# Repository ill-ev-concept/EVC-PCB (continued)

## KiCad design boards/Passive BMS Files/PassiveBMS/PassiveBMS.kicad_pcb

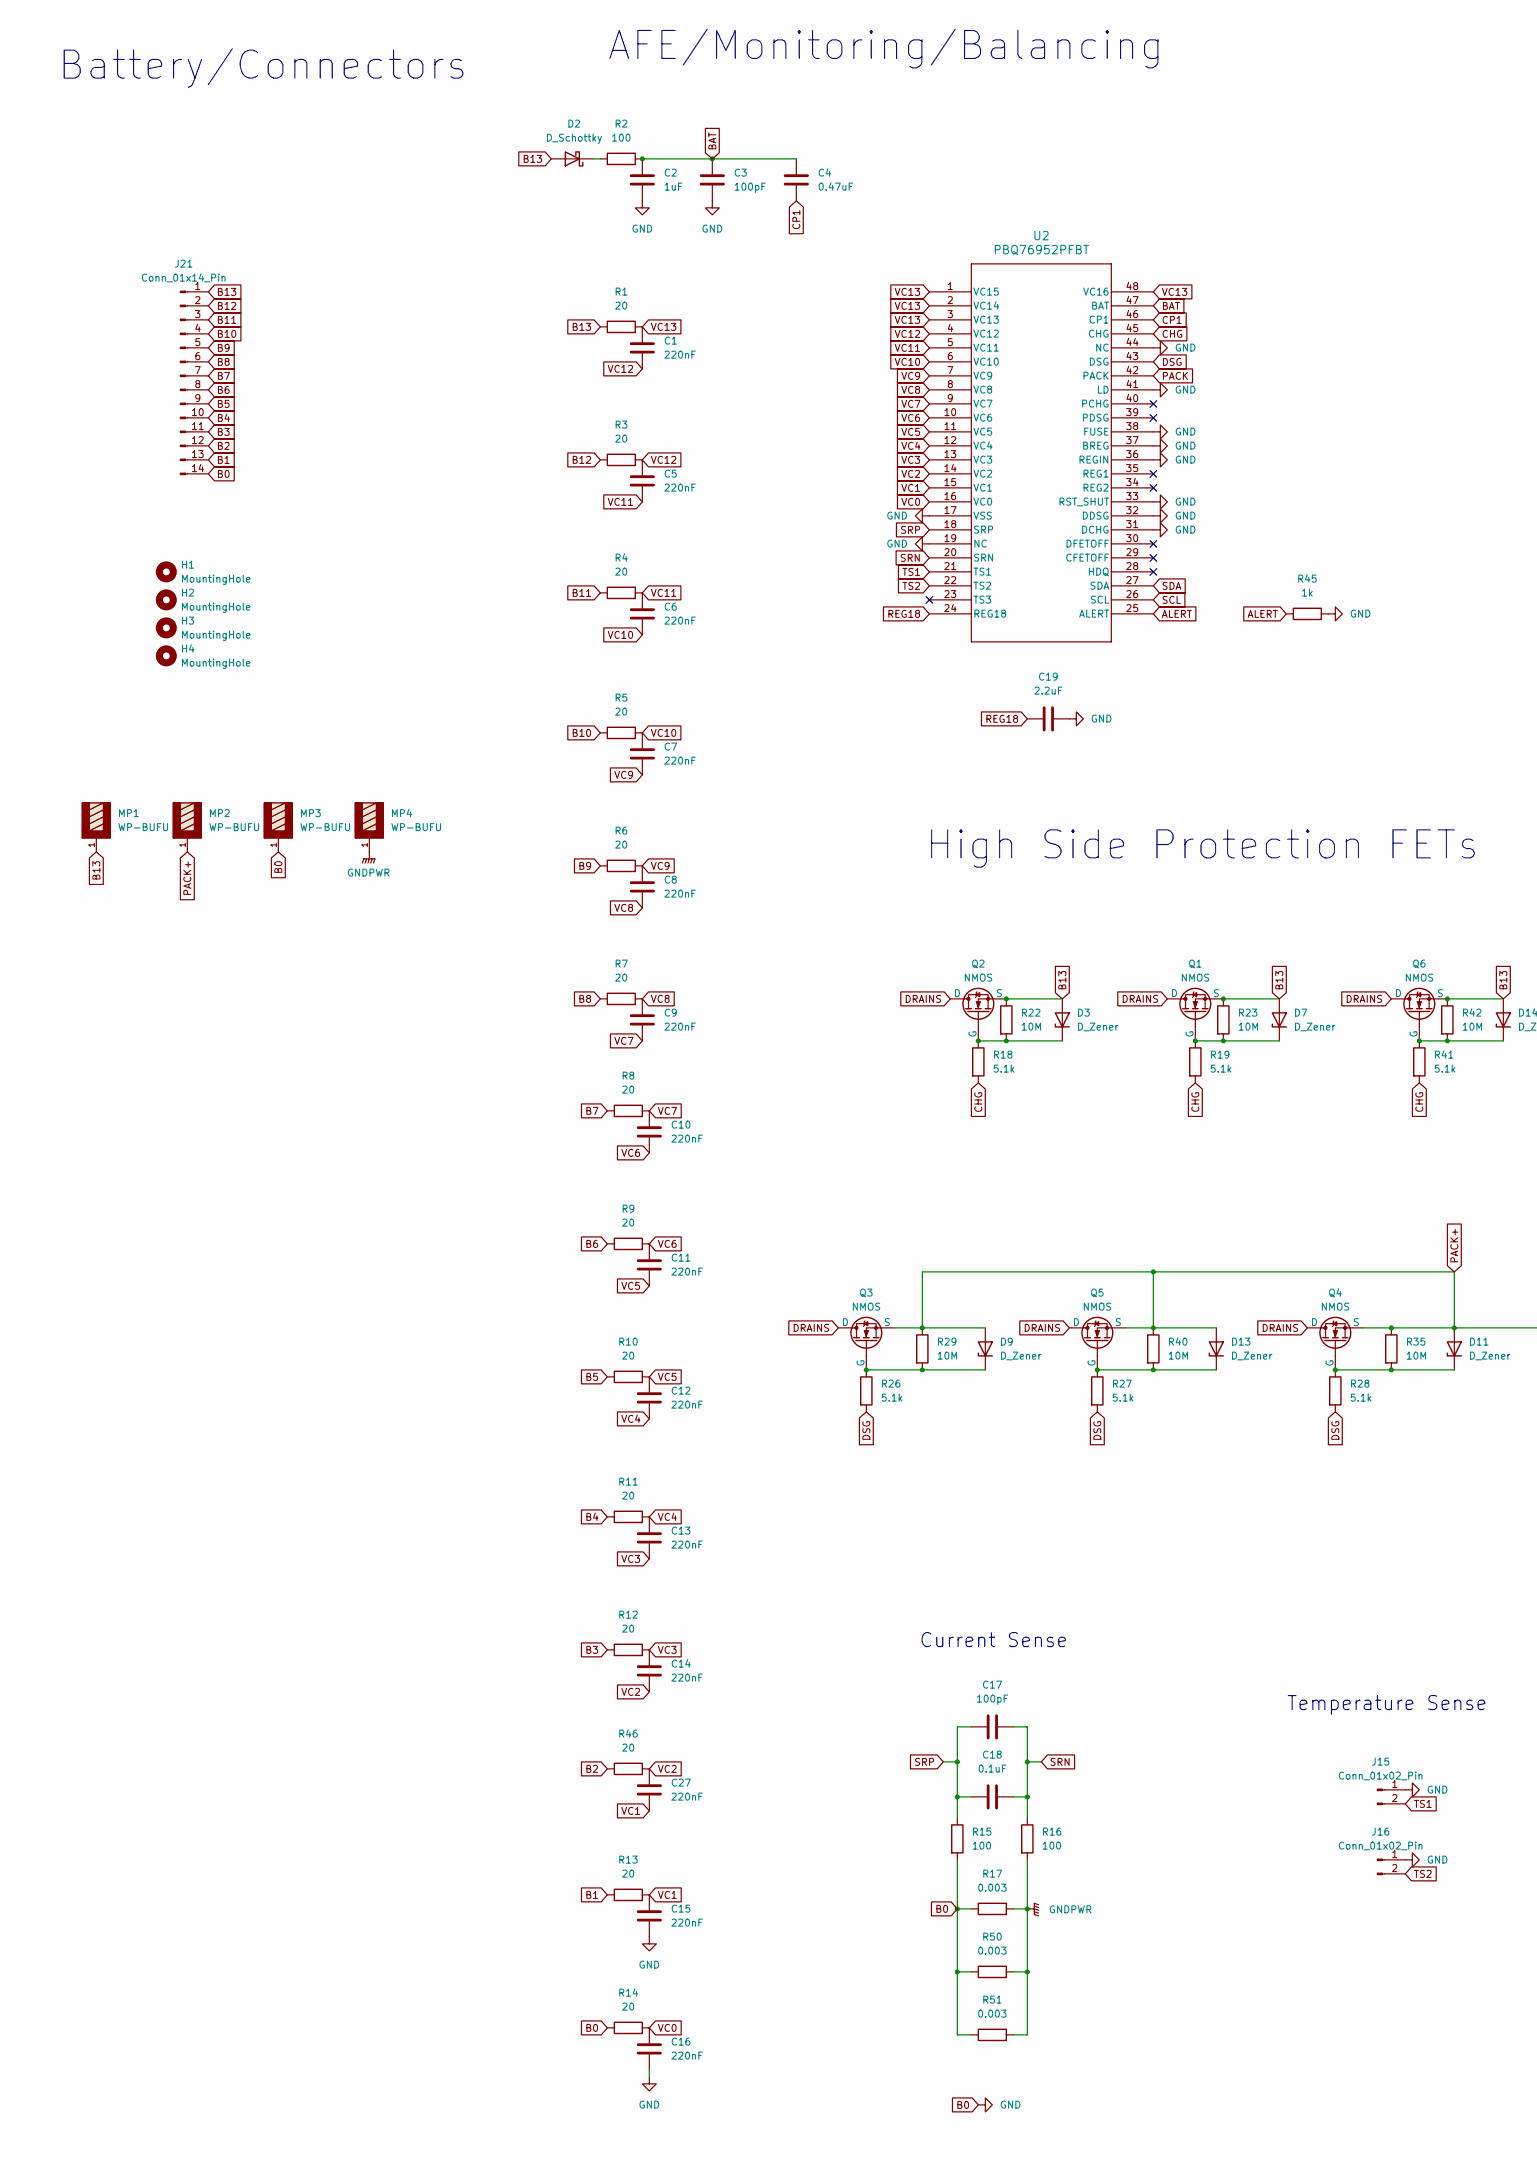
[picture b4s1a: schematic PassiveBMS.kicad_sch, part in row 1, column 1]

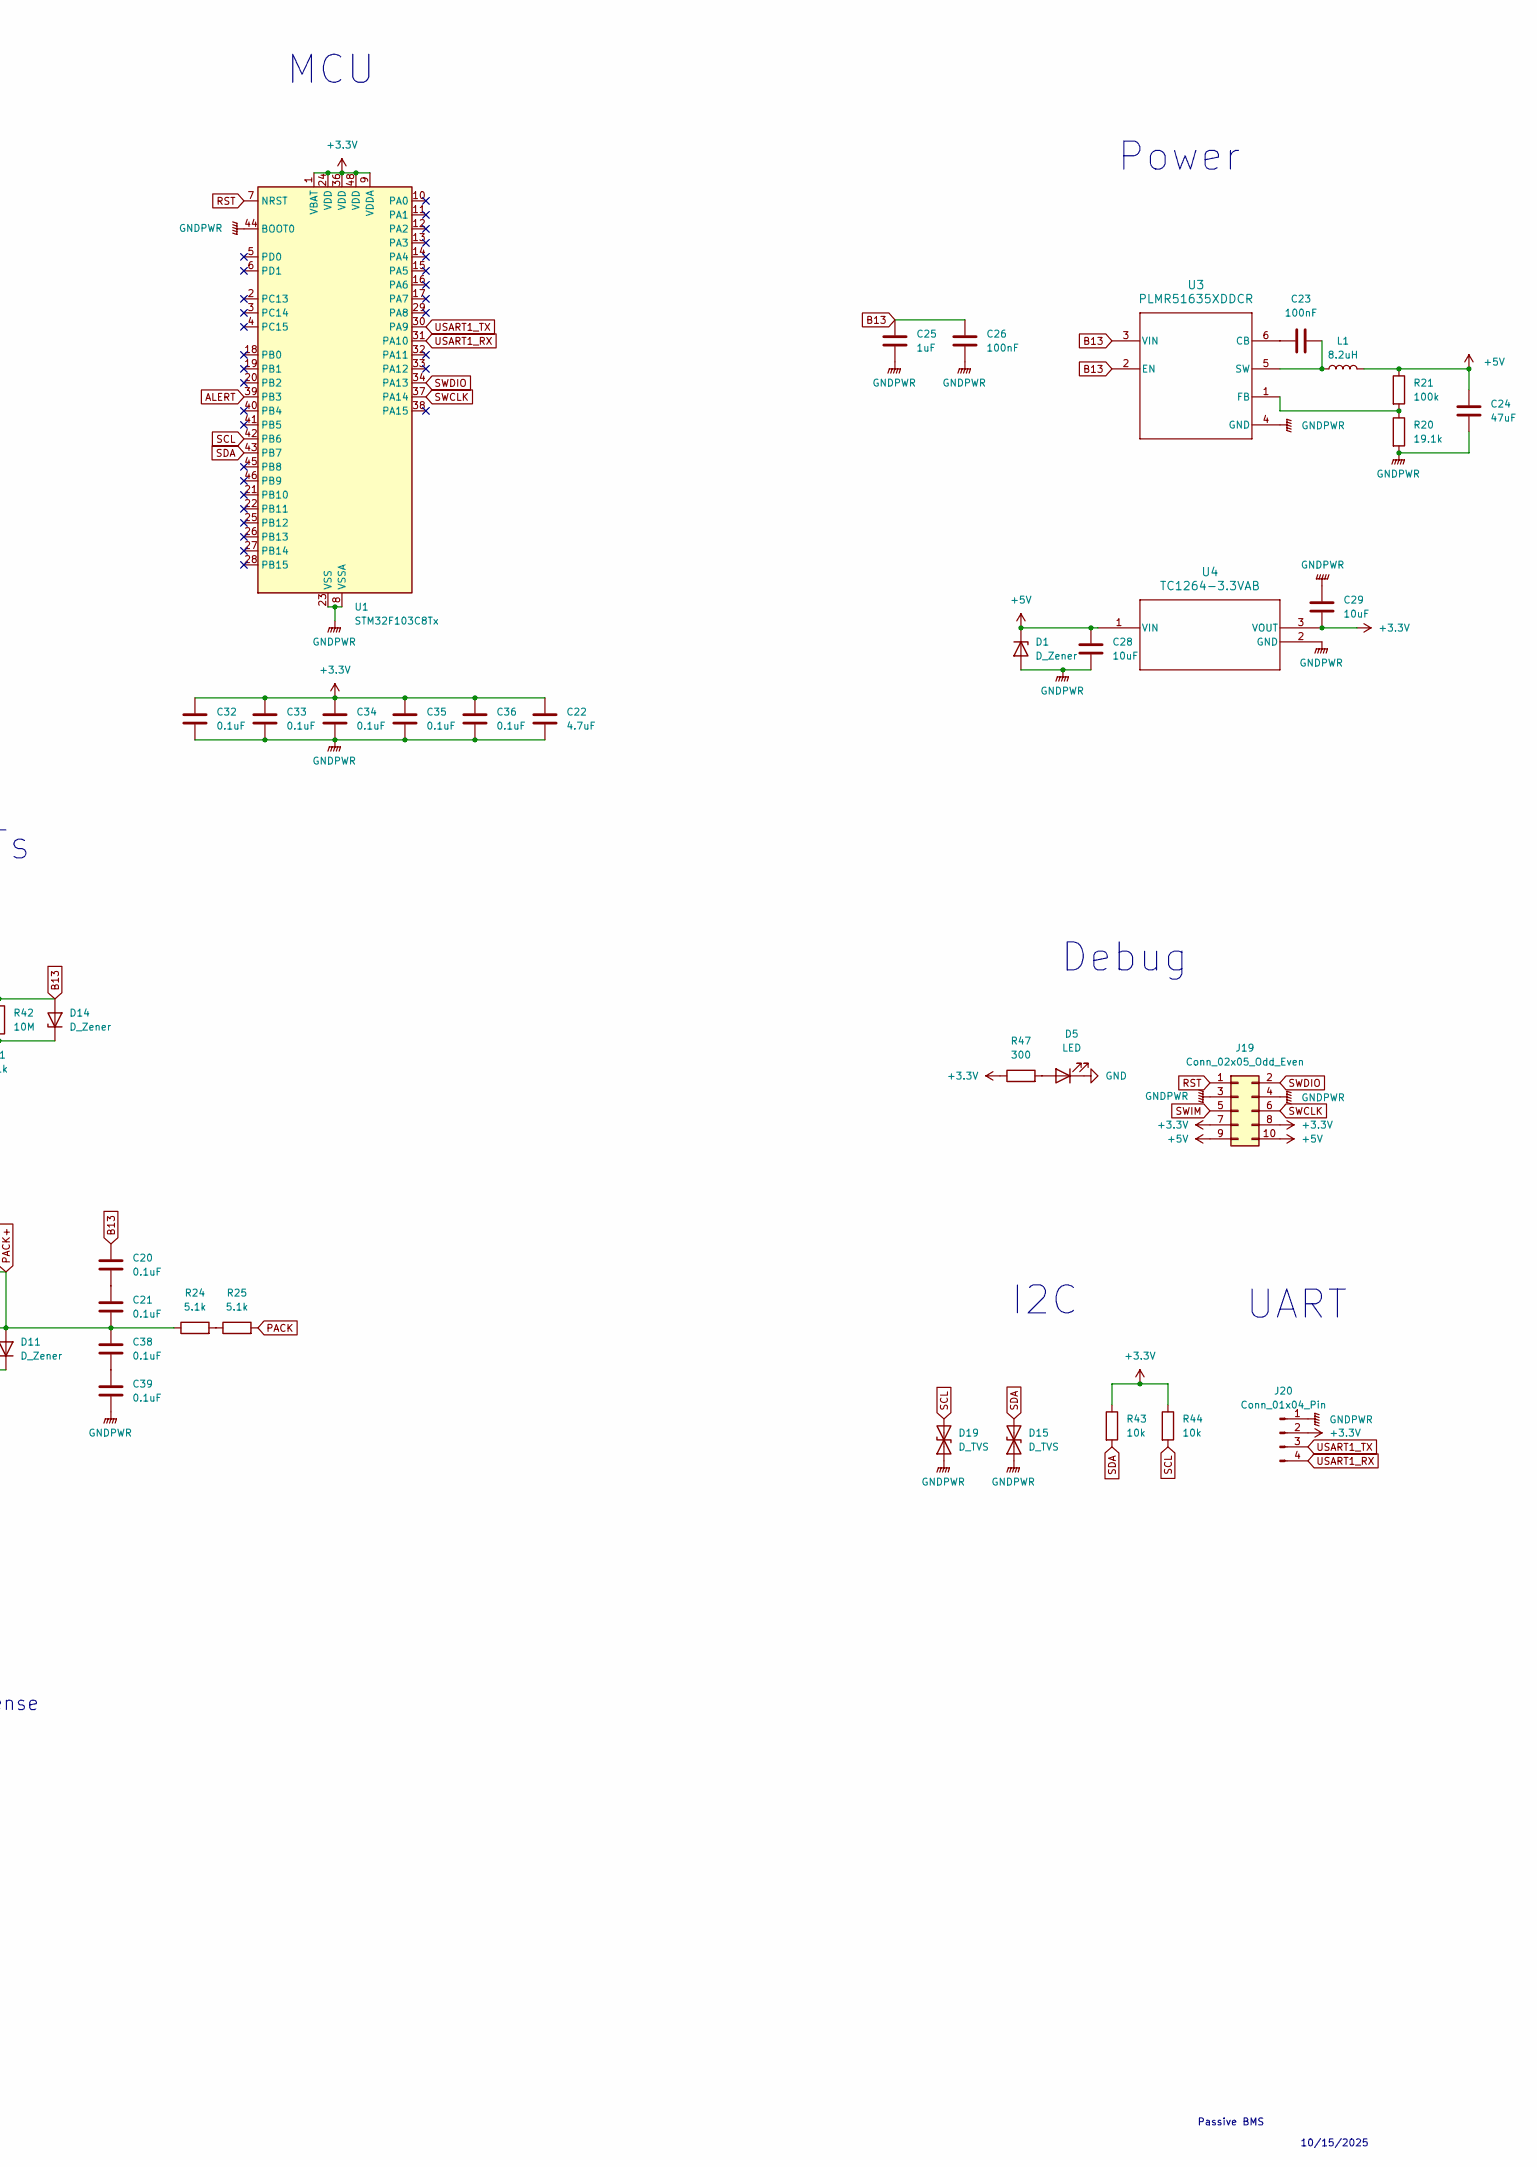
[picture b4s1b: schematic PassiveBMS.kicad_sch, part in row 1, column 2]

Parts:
C1, C5, C6, C7, C8, C9, C10, C11, C12, C13, C14, C15, C16, C27: 220nF; C_0402_1005Metric
C2, C25: 1uF; C_1206_3216Metric
C3: 100pF; C_1206_3216Metric
C4: 0.47uF; C_1206_3216Metric
C17: 100pF; C_0603_1608Metric
C18, C20, C21, C32, C33, C34, C35, C36: 0.1uF; C_0603_1608Metric
C19: 2.2uF; C_0603_1608Metric
C22: 4.7uF; C_0603_1608Metric
C23, C26: 100nF; C_1206_3216Metric
C24: 47uF; C_0402_1005Metric
C28, C29: 10uF; C_0603_1608Metric
C38, C39: 0.1uF; R_1206_3216Metric
D1: D_Zener; R_0805_2012Metric
D2: D_Schottky; D_SOD-123F
D3, D7, D9, D11, D13, D14: D_Zener; D_SOD-123
D5: LED; LED_0603_1608Metric
D15, D19: D_TVS; D_SOD-323
H1, H2, H3, H4: MountingHole; MountingHole_2.5mm
J15, J16: Conn_01x02_Pin; PinHeader_1x02_P2.54mm_Vertical
J19: Conn_02x05_Odd_Even; PinHeader_2x05_P2.54mm_Vertical
J20: Conn_01x04_Pin; PinHeader_1x04_P2.54mm_Vertical
J21: Conn_01x14_Pin; PinHeader_1x14_P2.54mm_Vertical
L1: 8.2uH; L_Bourns_SRR1260
MP1, MP2, MP3, MP4: WP-BUFU; screw connector
Q1, Q2, Q3, Q4, Q5, Q6: NMOS; fets
R1, R3, R4, R5, R6, R7, R8, R9, R10, R11, R12, R13, R14, R46: 20; R_0402_1005Metric
R2, R15, R16: 100; R_0603_1608Metric
R17, R50, R51: 0.003; R_Shunt_Vishay_WSR2_WSR3_KelvinConnection
R18, R19, R24, R25, R26, R27, R28, R41: 5.1k; R_0603_1608Metric
R20: 19.1k; R_0603_1608Metric
R21: 100k; R_0603_1608Metric
R22, R23, R29, R35, R40, R42: 10M; R_0603_1608Metric
R43, R44: 10k; R_0603_1608Metric
R45: 1k; R_0603_1608Metric
R47: 300; R_0603_1608Metric
U1: STM32F103C8Tx; LQFP-48_7x7mm_P0.5mm
U2: PBQ76952PFBT; TQFP-48_7x7mm_P0.5mm
U3: PLMR51635XDDCR; DDC0006A-MFG
U4: TC1264-3.3VAB; SOT-223-3_TabPin2

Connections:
+3.3V: C22.1, C29.2, C32.1, C33.1, C34.1, C35.1, C36.1, J19.7, J19.8, J20.2, R43.1, R44.1, R47.1, U1.1 (VBAT), U1.9 (VDDA), U1.24 (VDD), U1.36 (VDD), U1.48 (VDD), U4.3 (VOUT)
+5V: C24.2, C28.1, D1.1 (K), J19.9, J19.10, L1.2, R21.1, U4.1 (VIN)
ALERT: R45.1, U1.39 (PB3), U2.25 (ALERT)
B0: C2.2, C3.2, C15.2, C16.2, C19.2, D5.1 (K), J15.1, J16.1, J21.14, MP3.1, MP3.2, MP3.3, MP3.4, MP3.5, MP3.6, MP3.7, MP3.8, MP3.9, MP3.10, MP3.11, MP3.12, MP3.13, MP3.14, MP3.15, MP3.16, R14.1, R15.2, R17.1, R45.2, R50.1, R51.1, U2.17 (VSS), U2.19 (NC), U2.31 (DCHG), U2.32 (DDSG), U2.33 (RST_SHUT), U2.36 (REGIN), U2.37 (BREG), U2.38 (FUSE), U2.41 (LD), U2.44 (NC)
B1: J21.13, R13.1
B2: J21.12, R46.1
B3: J21.11, R12.1
B4: J21.10, R11.1
B5: J21.9, R10.1
B6: J21.8, R9.1
B7: J21.7, R8.1
B8: J21.6, R7.1
B9: J21.5, R6.1
B10: J21.4, R5.1
B11: J21.3, R4.1
B12: J21.2, R3.1
B13: C20.1, C25.1, C26.1, D2.2 (A), D3.2 (A), D7.2 (A), D14.2 (A), J21.1, MP1.1, MP1.2, MP1.3, MP1.4, MP1.5, MP1.6, MP1.7, MP1.8, MP1.9, MP1.10, MP1.11, MP1.12, MP1.13, MP1.14, MP1.15, MP1.16, Q1.3 (S), Q2.3 (S), Q6.3 (S), R1.1, R22.1, R23.1, R42.1, U3.2 (EN), U3.3 (VIN)
BAT: C2.1, C3.1, C4.1, R2.2, U2.47 (BAT)
CHG: R18.2, R19.2, R41.2, U2.45 (CHG)
CP1: C4.2, U2.46 (CP1)
DRAINS: Q1.1 (D), Q2.1 (D), Q3.1 (D), Q4.1 (D), Q5.1 (D), Q6.1 (D)
DSG: R26.2, R27.2, R28.2, U2.43 (DSG)
GNDPWR: C22.2, C24.1, C25.2, C26.2, C28.2, C29.1, C32.2, C33.2, C34.2, C35.2, C36.2, C39.2, D1.2 (A), D15.1 (A1), D19.1 (A1), J19.3, J19.4, J20.1, MP4.1, MP4.2, MP4.3, MP4.4, MP4.5, MP4.6, MP4.7, MP4.8, MP4.9, MP4.10, MP4.11, MP4.12, MP4.13, MP4.14, MP4.15, MP4.16, R16.2, R17.2, R20.2, R50.2, R51.2, U1.8 (VSSA), U1.23 (VSS), U1.35 (VSS), U1.44 (BOOT0), U1.47 (VSS), U3.4 (GND), U4.2 (GND)
unnamed: C20.2, C21.1
unnamed: C38.2, C39.1
unnamed: D2.1 (K), R2.1
unnamed: D3.1 (K), Q2.2 (G), R18.1, R22.2
unnamed: D5.2 (A), R47.2
unnamed: D7.1 (K), Q1.2 (G), R19.1, R23.2
unnamed: D9.1 (K), Q3.2 (G), R26.1, R29.2
unnamed: D11.1 (K), Q4.2 (G), R28.1, R35.2
unnamed: D13.1 (K), Q5.2 (G), R27.1, R40.2
unnamed: D14.1 (K), Q6.2 (G), R41.1, R42.2
unnamed: R24.2, R25.1
unnamed: C23.1, U3.6 (CB)
unnamed: R20.1, R21.2, U3.1 (FB)
unnamed: C23.2, L1.1, U3.5 (SW)
PACK: R25.2, U2.42 (PACK)
PACK+: C21.2, C38.1, D9.2 (A), D11.2 (A), D13.2 (A), MP2.1, MP2.2, MP2.3, MP2.4, MP2.5, MP2.6, MP2.7, MP2.8, MP2.9, MP2.10, MP2.11, MP2.12, MP2.13, MP2.14, MP2.15, MP2.16, Q3.3 (S), Q4.3 (S), Q5.3 (S), R24.1, R29.1, R35.1, R40.1
REG18: C19.1, U2.24 (REG18)
RST: J19.1, U1.7 (NRST)
SCL: D19.2 (A2), R44.2, U1.42 (PB6), U2.26 (SCL)
SDA: D15.2 (A2), R43.2, U1.43 (PB7), U2.27 (SDA)
SRN: C17.1, C18.1, R16.1, U2.20 (SRN)
SRP: C17.2, C18.2, R15.1, U2.18 (SRP)
SWCLK: J19.6, U1.37 (PA14)
SWDIO: J19.2, U1.34 (PA13)
SWIM: J19.5
TS1: J15.2, U2.21 (TS1)
TS2: J16.2, U2.22 (TS2)
USART1_RX: J20.4, U1.31 (PA10)
USART1_TX: J20.3, U1.30 (PA9)
VC0: C16.1, R14.2, U2.16 (VC0)
VC1: C15.1, C27.2, R13.2, U2.15 (VC1)
VC2: C14.2, C27.1, R46.2, U2.14 (VC2)
VC3: C13.2, C14.1, R12.2, U2.13 (VC3)
VC4: C12.2, C13.1, R11.2, U2.12 (VC4)
VC5: C11.2, C12.1, R10.2, U2.11 (VC5)
VC6: C10.2, C11.1, R9.2, U2.10 (VC6)
VC7: C9.2, C10.1, R8.2, U2.9 (VC7)
VC8: C8.2, C9.1, R7.2, U2.8 (VC8)
VC9: C7.2, C8.1, R6.2, U2.7 (VC9)
VC10: C6.2, C7.1, R5.2, U2.6 (VC10)
VC11: C5.2, C6.1, R4.2, U2.5 (VC11)
VC12: C1.2, C5.1, R3.2, U2.4 (VC12)
VC13: C1.1, R1.2, U2.1 (VC15), U2.2 (VC14), U2.3 (VC13), U2.48 (VC16)

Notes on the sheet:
Passive BMS
UART
Battery/Connectors
Debug
AFE/Monitoring/Balancing
Power
I2C
High Side Protection FETs
Temperature Sense
MCU
Current Sense
10/15/2025

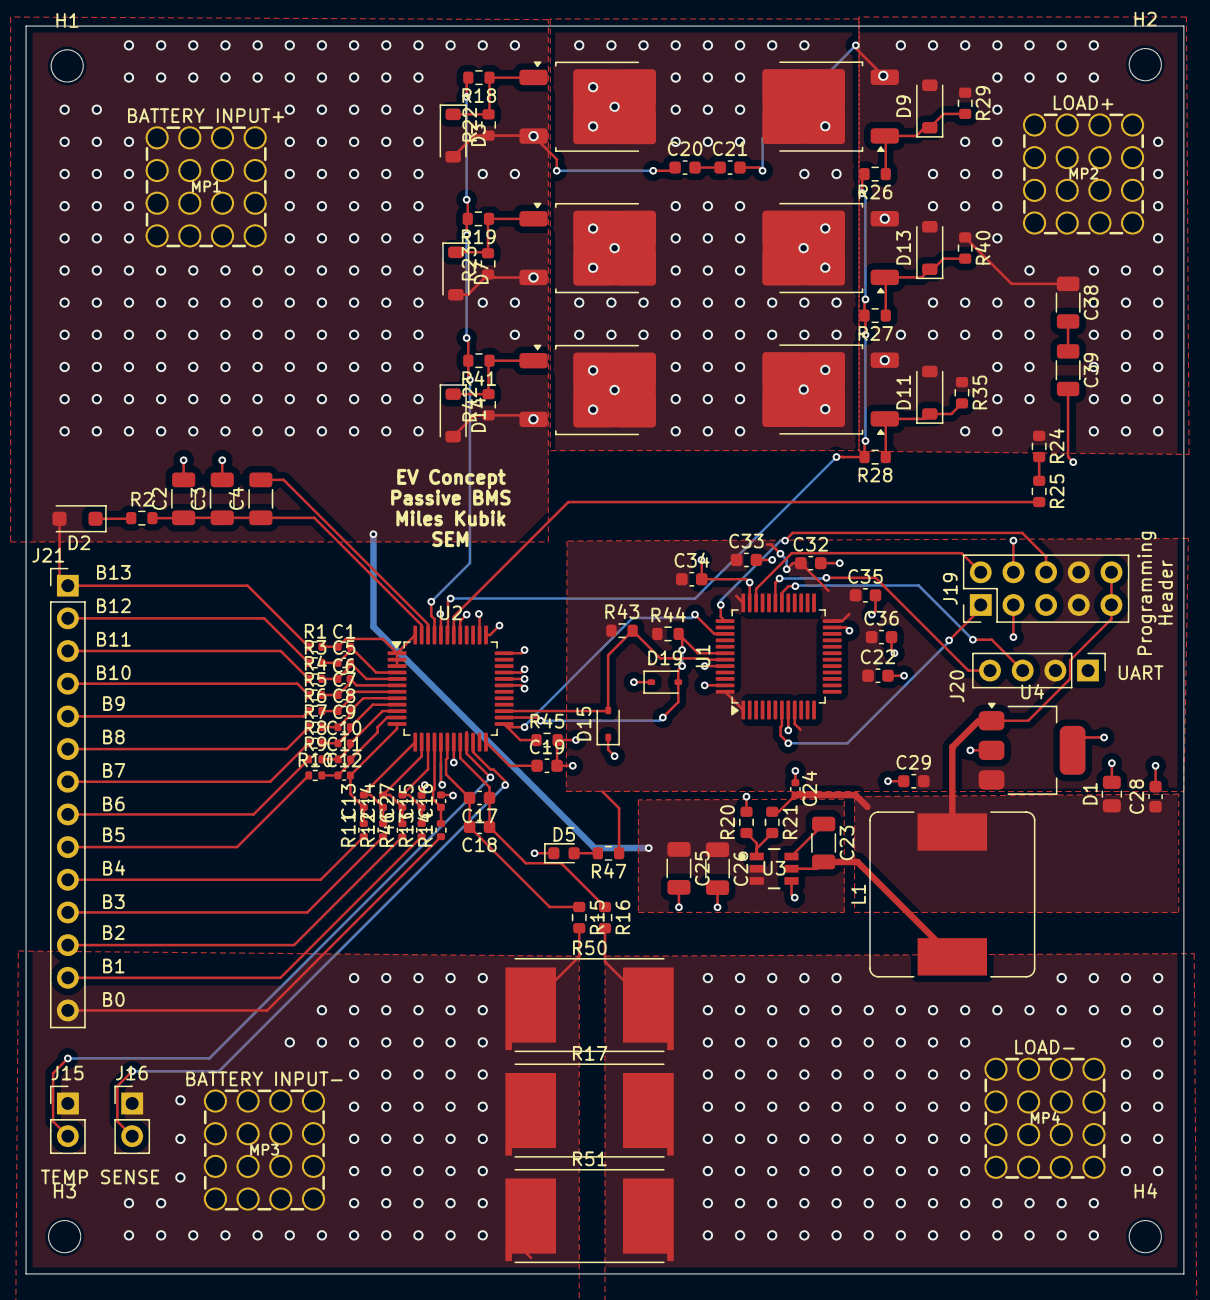
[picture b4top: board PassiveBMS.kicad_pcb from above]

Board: 2 copper layers, 90.0 x 97.0 mm, 111 parts (0 on the bottom side), 65 nets.

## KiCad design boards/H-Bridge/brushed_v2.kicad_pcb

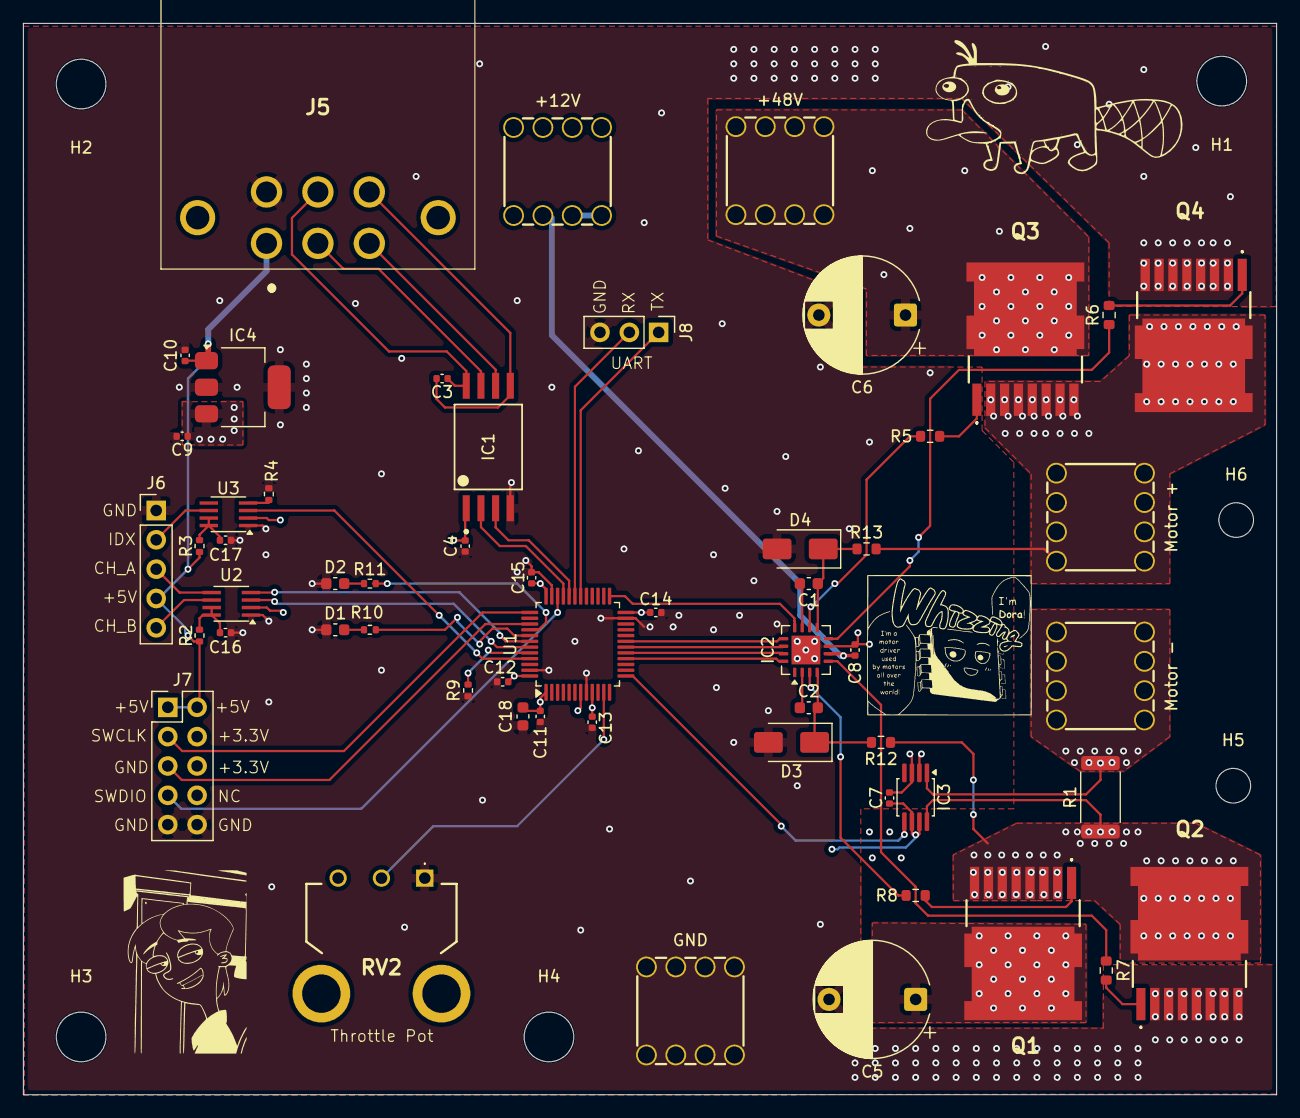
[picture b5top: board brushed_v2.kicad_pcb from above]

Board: 4 copper layers, 108.5 x 92.8 mm, 62 parts (0 on the bottom side), 52 nets.

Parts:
+12V: 12V+; WP-BUTR_7460307
+48V: V+; WP-BUTR_7460307
C1: 1uf; C_0603_1608Metric
C2: 1uF; C_0603_1608Metric
C3, C4, C7, C8, C11, C12, C13, C14, C15, C16, C17: 0.1uF; C_0402_1005Metric
C5, C6: 470uF; CP_Radial_D10.0mm_P7.50mm
C9, C10: 1uF; C_0402_1005Metric
C18: 4.7uF; C_0603_1608Metric
D1, D2: LED; C_0603_1608Metric
D3, D4: SS1200; D_SMA
GND: V-; WP-BUTR_7460307
H1, H2, H3, H4: MountingHole; MountingHole_4.3mm_M4
H5, H6: MountingHole; MountingHole_3mm
IC1: ISO1042QDWVQ1; DWV0008A-IPC_A
IC2: MIC4606-1YML-TR; QFN-16-1EP_4x4mm_P0.65mm_EP2.5x2.5mm
IC3: AD8410AWBRZ-RL; MSOP-8_3x3mm_P0.65mm
IC4: TC1108-3.3VDBTR; SOT-223
J5: DTF13-6P; DTF136P
J6: Encoder; PinHeader_1x05_P2.54mm_Vertical
J7: Prog_Header; PinHeader_2x05_P2.54mm_Vertical
J8: UART; PinHeader_1x03_P2.54mm_Vertical
Motor +: Motor-; WP-BUTR_7460307
Motor -: Motor+; WP-BUTR_7460307
Q1, Q2, Q3, Q4: NTBLS4D0N15MC
R1: .001; R_2512_6332Metric
R2, R3: 200k; R_0402_1005Metric
R4, R9: 10k; R_0402_1005Metric
R5, R6, R7, R8: 10; R_0603_1608Metric
R10, R11: 330; R_0402_1005Metric
R12, R13: 3; R_0603_1608Metric
RV2: Debug Throttle; P120PKY25BR10K
U1: STM32F103C8Tx; LQFP-48_7x7mm_P0.5mm
U2, U3: LSF0102DCUR; SSOP-8_2.95x2.8mm_P0.65mm

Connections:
+3.3V: C4.1, C7.1, C9.1, C11.1, C12.1, C13.1, C14.1, C15.1, C18.1, IC1.1 (VCC1), IC3.6 (VS), IC3.7 (VREF1), IC4.3 (VOUT), J7.4, J7.6, RV2.3, U1.1 (VBAT), U1.7 (NRST), U1.9 (VDDA), U1.24 (VDD), U1.36 (VDD), U1.48 (VDD), U2.2 (VREF_A), U3.2 (VREF_A)
+5V: C10.1, IC4.1 (VIN), J5.1, J6.4, J7.1, J7.2, R2.1, R3.1
+12V: +12V.1 (Pin_1_1), C8.1, IC2.6 (VDD)
+48V: +48V.1 (Pin_1_1), C5.1, C6.1, Q1.9 (D_1), Q1.10 (D_2), Q1.11 (D_3), Q1.12 (D_4), Q1.13 (D_5), Q3.9 (D_1), Q3.10 (D_2), Q3.11 (D_3), Q3.12 (D_4), Q3.13 (D_5)
/High Voltage&Sense/AHS: C2.2, D3.1 (K), IC2.4 (AHS), R12.2
/High Voltage&Sense/BHS: C1.1, D4.1 (K), IC2.9 (BHS), R13.1
/High Voltage&Sense/GATEA_HIGH: Q1.8 (G), R8.2
/High Voltage&Sense/GATEA_LOW: Q2.8 (G), R7.1
/High Voltage&Sense/GATEB_HIGH: Q3.8 (G), R5.2
/High Voltage&Sense/GATEB_LOW: Q4.8 (G), R6.2
/High Voltage&Sense/SHUNT+: IC3.8 (+IN), Q1.1 (S_1), Q1.2 (S_2), Q1.3 (S_3), Q1.4 (S_4), Q1.5 (S_5), Q1.6 (S_6), Q1.7 (S_7), Q2.9 (D_1), Q2.10 (D_2), Q2.11 (D_3), Q2.12 (D_4), Q2.13 (D_5), R1.1, R12.1
/High Voltage&Sense/SHUNT-: IC3.1 (-IN), Motor -.1 (Pin_1_1), R1.2
/MCU&Low_Voltage/AHI: IC2.16 (AHI), U1.16 (PA6)
/MCU&Low_Voltage/ALI: IC2.15 (ALI), U1.17 (PA7)
/MCU&Low_Voltage/BHI: IC2.13 (BHI), U1.19 (PB1)
/MCU&Low_Voltage/BLI: IC2.14 (BLI), U1.18 (PB0)
/MCU&Low_Voltage/CAN5V: C3.1, IC1.8 (VCC2), J5.5
/MCU&Low_Voltage/CANGND: C3.2, IC1.5 (GND2), J5.4
/MCU&Low_Voltage/CANH: IC1.7 (CANH), J5.2
/MCU&Low_Voltage/CANL: IC1.6 (CANL), J5.3
/MCU&Low_Voltage/CAN_RX: IC1.3 (RXD), U1.32 (PA11)
/MCU&Low_Voltage/CAN_TX: IC1.2 (TXD), U1.33 (PA12)
/MCU&Low_Voltage/CHA_3.3: U1.42 (PB6), U2.4 (A2)
/MCU&Low_Voltage/CHB_3.3: U1.43 (PB7), U2.3 (A1)
/MCU&Low_Voltage/CH_A: J6.3, U2.5 (B2)
/MCU&Low_Voltage/CH_B: J6.5, U2.6 (B1)
/MCU&Low_Voltage/GATE_EN: IC2.12 (EN), U1.25 (PB12)
/MCU&Low_Voltage/IDX: J6.2, U3.6 (B1)
/MCU&Low_Voltage/IDX_3.3: U1.45 (PB8), U3.3 (A1)
/MCU&Low_Voltage/LED_1: R10.1, U1.41 (PB5)
/MCU&Low_Voltage/LED_2: R11.1, U1.40 (PB4)
/MCU&Low_Voltage/POT_IN: RV2.2, U1.11 (PA1)
/MCU&Low_Voltage/SENSE: IC3.5 (OUT), U1.13 (PA3)
/MCU&Low_Voltage/SWCLK: J7.3, U1.37 (PA14)
/MCU&Low_Voltage/SWDIO: J7.7, U1.34 (PA13)
/MCU&Low_Voltage/SWO: J7.5, U1.39 (PB3)
/MCU&Low_Voltage/UART_RX: J8.2, U1.31 (PA10)
/MCU&Low_Voltage/UART_TX: J8.1, U1.30 (PA9)
GND: C4.2, C5.2, C6.2, C7.2, C8.2, C9.2, C10.2, C11.2, C12.2, C13.2, C14.2, C15.2, C16.2, C17.2, C18.2, D1.1 (K), D2.1 (K), D3.2 (A), D4.2 (A), GND.1 (Pin_1_1), IC1.4 (GND1), IC2.7 (VSS), IC2.17 (GND), IC3.2 (GND), IC3.3 (VREF2), IC4.2 (GND_1), IC4.4 (GND_2), J5.6, J6.1, J7.9, J7.10, J8.3, Q2.1 (S_1), Q2.2 (S_2), Q2.3 (S_3), Q2.4 (S_4), Q2.5 (S_5), Q2.6 (S_6), Q2.7 (S_7), Q4.1 (S_1), Q4.2 (S_2), Q4.3 (S_3), Q4.4 (S_4), Q4.5 (S_5), Q4.6 (S_6), Q4.7 (S_7), R4.1, R9.2, RV2.1, U1.8 (VSSA), U1.23 (VSS), U1.35 (VSS), U1.47 (VSS), U2.1 (GND), U3.1 (GND)
unnamed: D1.2 (A), R10.2
unnamed: D2.2 (A), R11.2
unnamed: C2.1, IC2.2 (AHB)
unnamed: IC2.3 (AHO), R8.1
unnamed: IC2.5 (ALO), R7.2
unnamed: C1.2, IC2.11 (BHB)
unnamed: IC2.10 (BHO), R5.1
unnamed: IC2.8 (BLO), R6.1
unnamed: Motor +.1 (Pin_1_1), Q3.1 (S_1), Q3.2 (S_2), Q3.3 (S_3), Q3.4 (S_4), Q3.5 (S_5), Q3.6 (S_6), Q3.7 (S_7), Q4.9 (D_1), Q4.10 (D_2), Q4.11 (D_3), Q4.12 (D_4), Q4.13 (D_5), R13.2
unnamed: R9.1, U1.44 (BOOT0)
unnamed: C16.1, R2.2, U2.7 (VREF_B), U2.8 (EN)
unnamed: R4.2, U3.4 (A2)
unnamed: C17.1, R3.2, U3.7 (VREF_B), U3.8 (EN)

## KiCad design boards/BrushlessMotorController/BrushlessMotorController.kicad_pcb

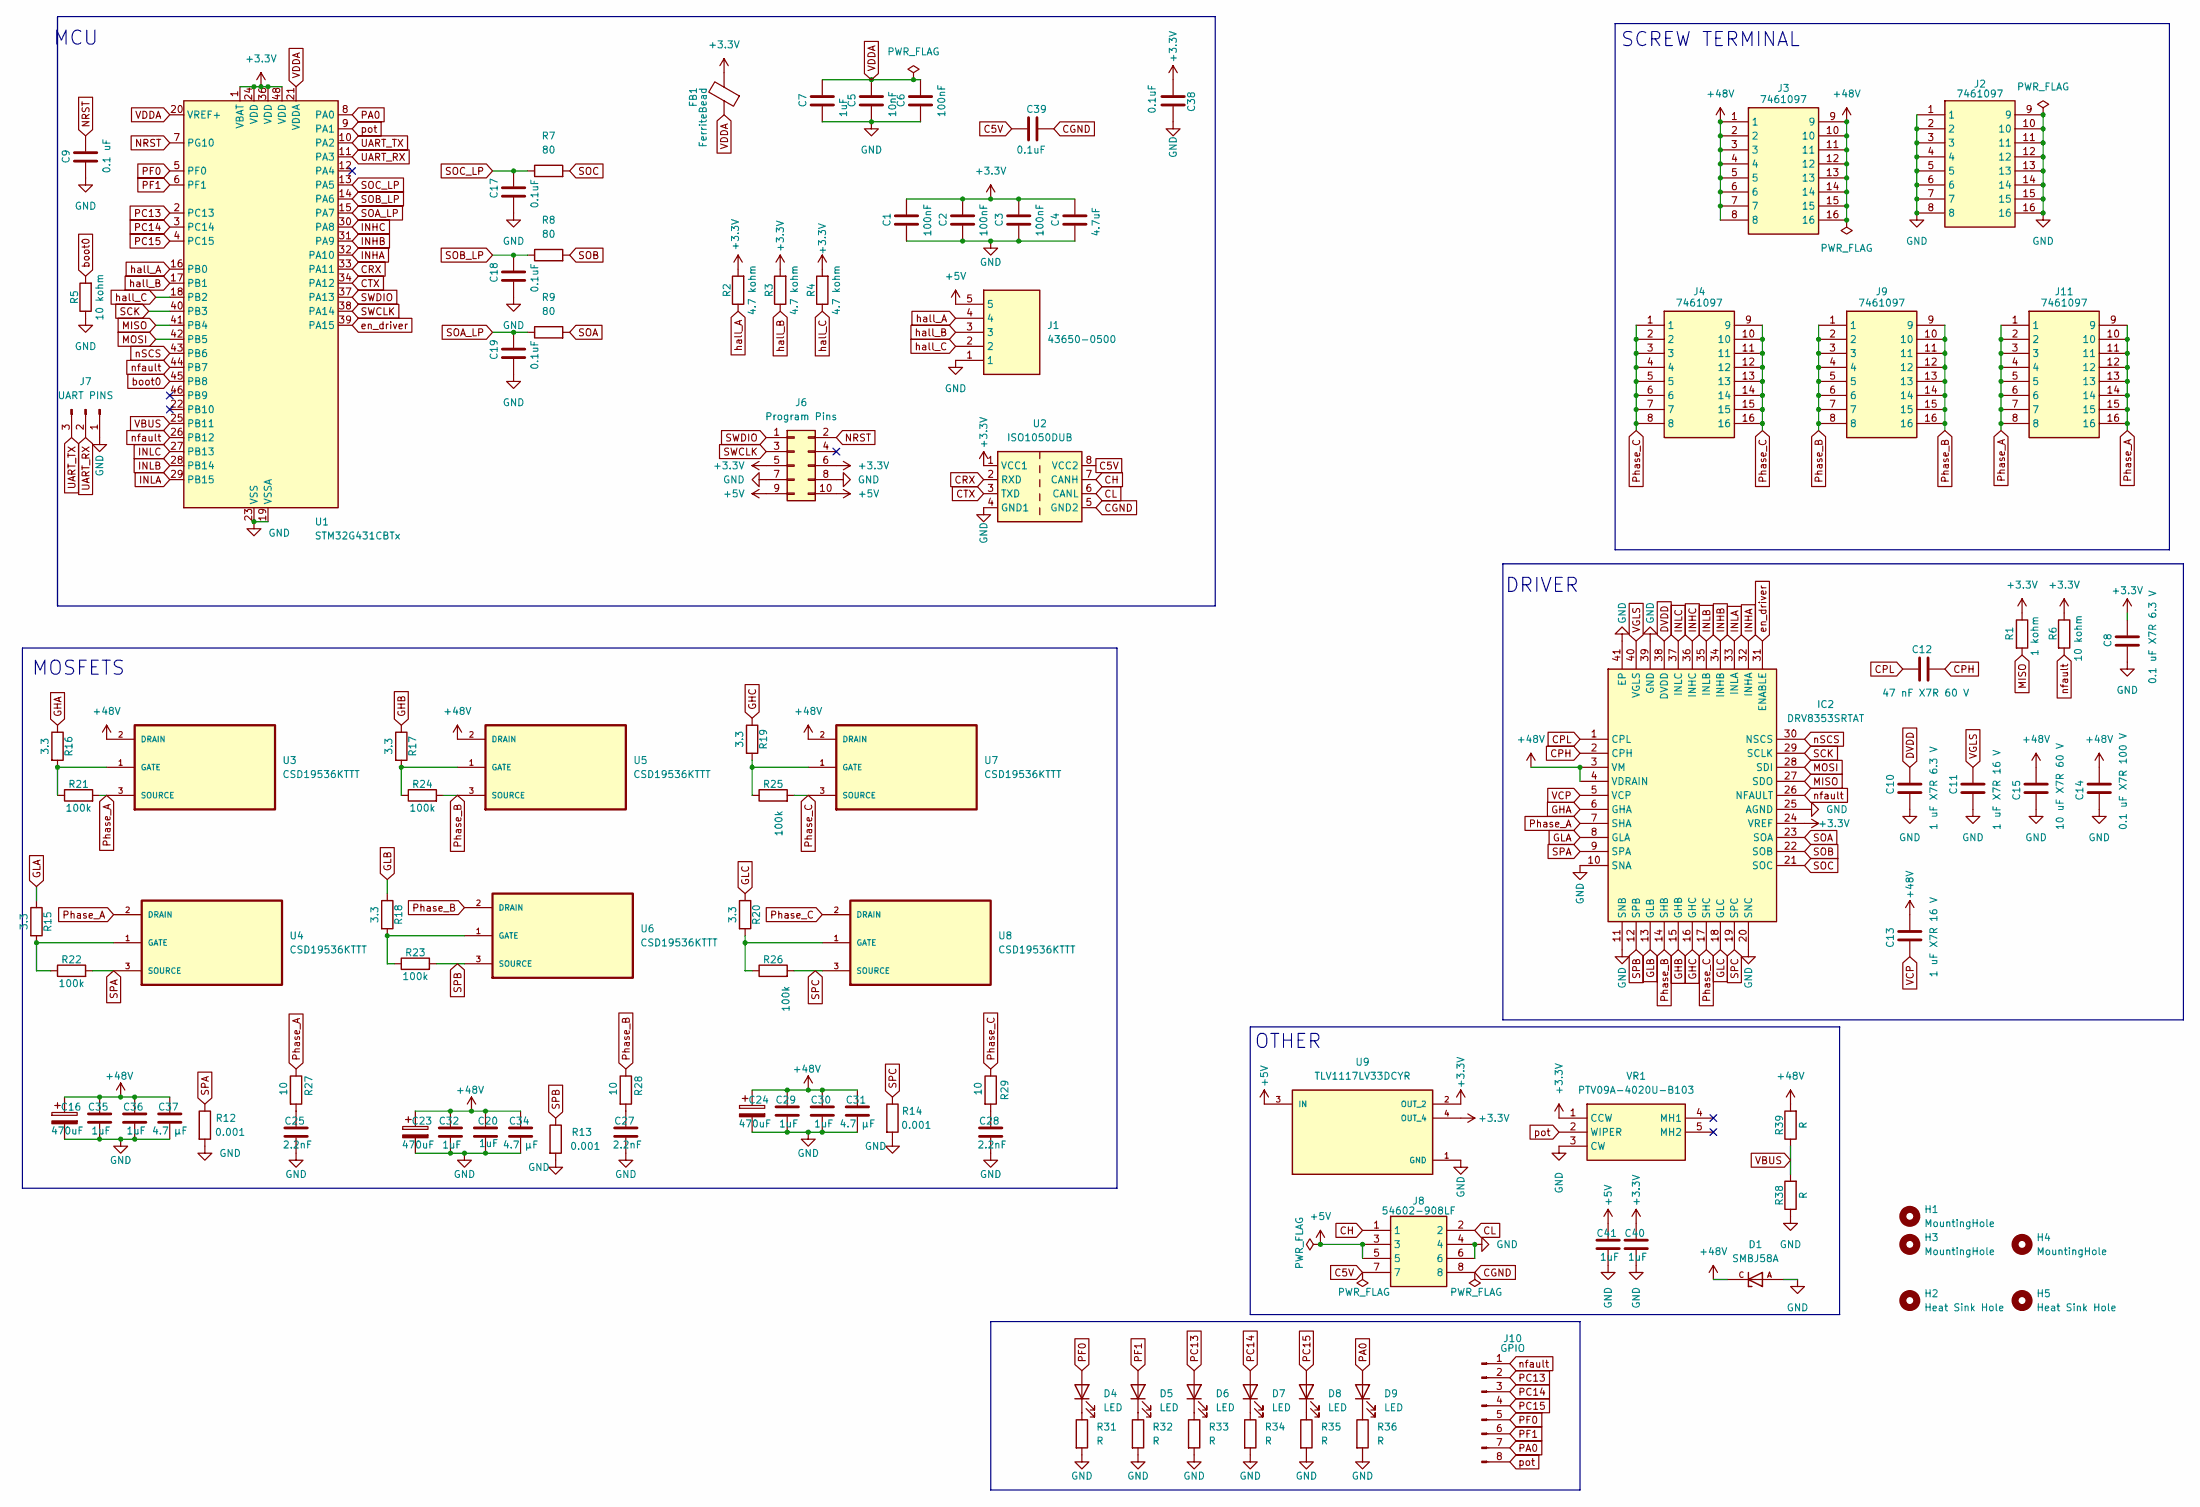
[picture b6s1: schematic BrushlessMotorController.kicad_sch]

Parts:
C1, C2, C3, C6: 100nF; C_0805_2012Metric_Pad1.18x1.45mm_HandSolder
C4: 4.7uF; C_0805_2012Metric_Pad1.18x1.45mm_HandSolder
C5: 10nF; C_0805_2012Metric_Pad1.18x1.45mm_HandSolder
C7, C40, C41: 1uF; C_0805_2012Metric_Pad1.18x1.45mm_HandSolder
C8: 0.1 uF X7R 6.3 V; C_0805_2012Metric_Pad1.18x1.45mm_HandSolder
C9: 0.1 uF; C_0805_2012Metric_Pad1.18x1.45mm_HandSolder
C10: 1 uF X7R 6.3 V; C_0805_2012Metric_Pad1.18x1.45mm_HandSolder
C11, C13: 1 uF X7R 16 V; C_0805_2012Metric_Pad1.18x1.45mm_HandSolder
C12: 47 nF X7R 60 V; C_0805_2012Metric_Pad1.18x1.45mm_HandSolder
C14: 0.1 uF X7R 100 V; C_0805_2012Metric_Pad1.18x1.45mm_HandSolder
C15: 10 uF X7R 60 V; C_1210_3225Metric_Pad1.33x2.70mm_HandSolder
C16, C23, C24: 470uF; CP_Radial_D16.0mm_P7.50mm
C17, C18, C19: 0.1uF; C_0603_1608Metric_Pad1.08x0.95mm_HandSolder
C20, C29, C30, C32, C35, C36: 1uF; C_1210_3225Metric
C25, C27, C28: 2.2nF; C_1210_3225Metric
C31, C34, C37: 4.7 µF; C_1210_3225Metric
C38, C39: 0.1uF; C_0805_2012Metric_Pad1.18x1.45mm_HandSolder
D1: SMBJ58A; DIOM4336X265N; PARTREV F2102
D4, D5, D6, D7, D8, D9: LED; LED_0603_1608Metric_Pad1.05x0.95mm_HandSolder
FB1: FerriteBead; R_0805_2012Metric_Pad1.20x1.40mm_HandSolder
H1, H3, H4: MountingHole; MountingHole_3.2mm_M3
H2, H5: Heat Sink Hole; MountingHole_3.2mm_M3
IC2: DRV8353SRTAT; QFN50P600X600X80-41N; Mouser Part Number 595-DRV8353SRTAT
J1: 43650-0500; 43650-05_00,01,02_; Mouser Part Number 538-43650-0500
J2, J3, J4, J9, J11: 7461097; Mouser Part Number 710-7461097
J6: Program Pins; PinHeader_2x05_P2.54mm_Vertical
J7: UART PINS; PinHeader_1x03_P2.54mm_Vertical
J8: 54602-908LF; 54602908LF; Manufacturer_Part_Number 54602-908LF
J10: GPIO; PinHeader_1x08_P2.54mm_Vertical
R1: 1 kohm; R_0805_2012Metric_Pad1.20x1.40mm_HandSolder
R2, R3, R4: 4.7 kohm; R_0805_2012Metric_Pad1.20x1.40mm_HandSolder
R5, R6: 10 kohm; R_0805_2012Metric_Pad1.20x1.40mm_HandSolder
R7, R8, R9: 80; R_0603_1608Metric
R12, R13, R14: 0.001; R_2512_6332Metric_Pad1.40x3.35mm_HandSolder
R15, R16, R17, R18, R19, R20: 3.3; R_0805_2012Metric_Pad1.20x1.40mm_HandSolder
R21, R22, R23, R24, R25, R26: 100k; R_0805_2012Metric_Pad1.20x1.40mm_HandSolder
R27, R28, R29: 10; R_0805_2012Metric_Pad1.20x1.40mm_HandSolder
R31, R32, R33, R34, R35, R36, R38, R39: R; R_0805_2012Metric_Pad1.20x1.40mm_HandSolder
U1: STM32G431CBTx; LQFP-48_7x7mm_P0.5mm
U2: ISO1050DUB; SOP-8_6.62x9.15mm_P2.54mm
U3, U4, U5, U6, U7, U8: CSD19536KTTT; TO254P1524X483-4N
U9: TLV1117LV33DCYR; VREG_TLV1117LV33DCYR; PARTREV B
VR1: PTV09A-4020U-B103; PTV09A4020UB103; Mouser Part Number 652-PTV09A-4020UB103

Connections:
+3.3V: C1.1, C2.1, C3.1, C4.1, C8.1, C38.2, C40.2, FB1.2, IC2.24 (VREF), J6.5, J6.6, R1.1, R2.2, R3.2, R4.2, R6.1, U1.1 (VBAT), U1.24 (VDD), U1.36 (VDD), U1.48 (VDD), U2.1 (VCC1), U9.2 (OUT_2), U9.4 (OUT_4), VR1.1 (CCW)
+5V: C41.2, J1.5, J6.9, J6.10, J8.3, J8.5, U9.3 (IN)
+48V: C13.1, C14.1, C15.1, C16.1, C20.1, C23.1, C24.1, C29.2, C30.2, C31.2, C32.2, C34.2, C35.2, C36.2, C37.2, D1.C, IC2.3 (VM), IC2.4 (VDRAIN), J3.1, J3.2, J3.3, J3.4, J3.5, J3.6, J3.7, J3.8, J3.9, J3.10, J3.11, J3.12, J3.13, J3.14, J3.15, J3.16, R39.2, U3.2 (DRAIN), U5.2 (DRAIN), U7.2 (DRAIN)
C5V: C39.2, J8.7, U2.8 (VCC2)
CGND: C39.1, J8.8, U2.5 (GND2)
CH: J8.1, U2.7 (CANH)
CL: J8.2, U2.6 (CANL)
CPH: C12.1, IC2.2 (CPH)
CPL: C12.2, IC2.1 (CPL)
CRX: U1.33 (PA11), U2.2 (RXD)
CTX: U1.34 (PA12), U2.3 (TXD)
DVDD: C10.1, IC2.38 (DVDD)
GHA: IC2.6 (GHA), R16.1
GHB: IC2.15 (GHB), R17.1
GHC: IC2.16 (GHC), R19.1
GLA: IC2.8 (GLA), R15.1
GLB: IC2.13 (GLB), R18.1
GLC: IC2.18 (GLC), R20.1
GND: C1.2, C2.2, C3.2, C4.2, C5.2, C6.2, C7.2, C8.2, C9.2, C10.2, C11.2, C14.2, C15.2, C16.2, C17.2, C18.2, C19.2, C20.2, C23.2, C24.2, C25.1, C27.1, C28.1, C29.1, C30.1, C31.1, C32.1, C34.1, C35.1, C36.1, C37.1, C38.1, C40.1, C41.1, D1.A, IC2.10 (SNA), IC2.11 (SNB), IC2.20 (SNC), IC2.25 (AGND), IC2.39 (GND), IC2.41 (EP), J1.1, J2.1, J2.2, J2.3, J2.4, J2.5, J2.6, J2.7, J2.8, J2.9, J2.10, J2.11, J2.12, J2.13, J2.14, J2.15, J2.16, J6.7, J6.8, J7.1, J8.4, J8.6, R5.1, R12.2, R13.2, R14.2, R31.2, R32.2, R33.2, R34.2, R35.2, R36.2, R38.1, U1.19 (VSSA), U1.23 (VSS), U1.35 (VSS), U1.47 (VSS), U2.4 (GND1), U9.1 (GND), VR1.3 (CW)
INHA: IC2.32 (INHA), U1.32 (PA10)
INHB: IC2.34 (INHB), U1.31 (PA9)
INHC: IC2.36 (INHC), U1.30 (PA8)
INLA: IC2.33 (INLA), U1.29 (PB15)
INLB: IC2.35 (INLB), U1.28 (PB14)
INLC: IC2.37 (INLC), U1.27 (PB13)
MISO: IC2.27 (SDO), R1.2, U1.41 (PB4)
MOSI: IC2.28 (SDI), U1.42 (PB5)
NRST: C9.1, J6.2, U1.7 (PG10)
unnamed: C25.2, R27.2
unnamed: C27.2, R28.2
unnamed: C28.2, R29.2
unnamed: D4.1 (K), R31.1
unnamed: D5.1 (K), R32.1
unnamed: D6.1 (K), R33.1
unnamed: D7.1 (K), R34.1
unnamed: D8.1 (K), R35.1
unnamed: D9.1 (K), R36.1
unnamed: R16.2, R21.1, U3.1 (GATE)
unnamed: R15.2, R22.1, U4.1 (GATE)
unnamed: R17.2, R24.1, U5.1 (GATE)
unnamed: R18.2, R23.1, U6.1 (GATE)
unnamed: R19.2, R25.1, U7.1 (GATE)
unnamed: R20.2, R26.1, U8.1 (GATE)
PA0: D9.2 (A), J10.7, U1.8 (PA0)
PC13: D6.2 (A), J10.2, U1.2 (PC13)
PC14: D7.2 (A), J10.3, U1.3 (PC14)
PC15: D8.2 (A), J10.4, U1.4 (PC15)
PF0: D4.2 (A), J10.5, U1.5 (PF0)
PF1: D5.2 (A), J10.6, U1.6 (PF1)
Phase_A: IC2.7 (SHA), J11.1, J11.2, J11.3, J11.4, J11.5, J11.6, J11.7, J11.8, J11.9, J11.10, J11.11, J11.12, J11.13, J11.14, J11.15, J11.16, R21.2, R27.1, U3.3 (SOURCE), U4.2 (DRAIN)
Phase_B: IC2.14 (SHB), J9.1, J9.2, J9.3, J9.4, J9.5, J9.6, J9.7, J9.8, J9.9, J9.10, J9.11, J9.12, J9.13, J9.14, J9.15, J9.16, R24.2, R28.1, U5.3 (SOURCE), U6.2 (DRAIN)
Phase_C: IC2.17 (SHC), J4.1, J4.2, J4.3, J4.4, J4.5, J4.6, J4.7, J4.8, J4.9, J4.10, J4.11, J4.12, J4.13, J4.14, J4.15, J4.16, R25.2, R29.1, U7.3 (SOURCE), U8.2 (DRAIN)
SCK: IC2.29 (SCLK), U1.40 (PB3)
SOA: IC2.23 (SOA), R9.2
SOA_LP: C19.1, R9.1, U1.15 (PA7)
SOB: IC2.22 (SOB), R8.2
SOB_LP: C18.1, R8.1, U1.14 (PA6)
SOC: IC2.21 (SOC), R7.2
SOC_LP: C17.1, R7.1, U1.13 (PA5)
SPA: IC2.9 (SPA), R12.1, R22.2, U4.3 (SOURCE)
SPB: IC2.12 (SPB), R13.1, R23.2, U6.3 (SOURCE)
SPC: IC2.19 (SPC), R14.1, R26.2, U8.3 (SOURCE)
SWCLK: J6.3, U1.38 (PA14)
SWDIO: J6.1, U1.37 (PA13)
UART_RX: J7.2, U1.11 (PA3)
UART_TX: J7.3, U1.10 (PA2)
VBUS: R38.2, R39.1, U1.25 (PB11)
VCP: C13.2, IC2.5 (VCP)
VDDA: C5.1, C6.1, C7.1, FB1.1, U1.20 (VREF+), U1.21 (VDDA)
VGLS: C11.1, IC2.40 (VGLS)
boot0: R5.2, U1.45 (PB8)
en_driver: IC2.31 (ENABLE), U1.39 (PA15)
hall_A: J1.4, R2.1, U1.16 (PB0)
hall_B: J1.3, R3.1, U1.17 (PB1)
hall_C: J1.2, R4.1, U1.18 (PB2)
nSCS: IC2.30 (NSCS), U1.43 (PB6)
nfault: IC2.26 (NFAULT), J10.1, R6.2, U1.26 (PB12), U1.44 (PB7)
pot: J10.8, U1.9 (PA1), VR1.2 (WIPER)

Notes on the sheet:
OTHER
SCREW TERMINAL
MOSFETS
MCU
DRIVER
